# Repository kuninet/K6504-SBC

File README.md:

# K6504-SBC

## 概要

* R6504 CPU(6502 CPUの仲間)を使ったシングルボードコンピューターです。
  * アドレシングできる範囲は8kBです。
  * RAM4kB、ROM3kB UniversanMonitorを動かすのが目標です

## 回路図

## 基板製造データ

* プリント基板を製造するには、KiCAD/PCB フォルダに入っているzipファイルをお使いください。

## 部品表

[KiCAD/K6504-SBC.csv](KiCAD/K6504-SBC.csv)

## 注意点

* シリアルIC(6551)、RAM/IO/TIMER IC(6532)の割り込み信号線は、基板裏のソルダージャンパーをはんだで短絡すると有効になります。

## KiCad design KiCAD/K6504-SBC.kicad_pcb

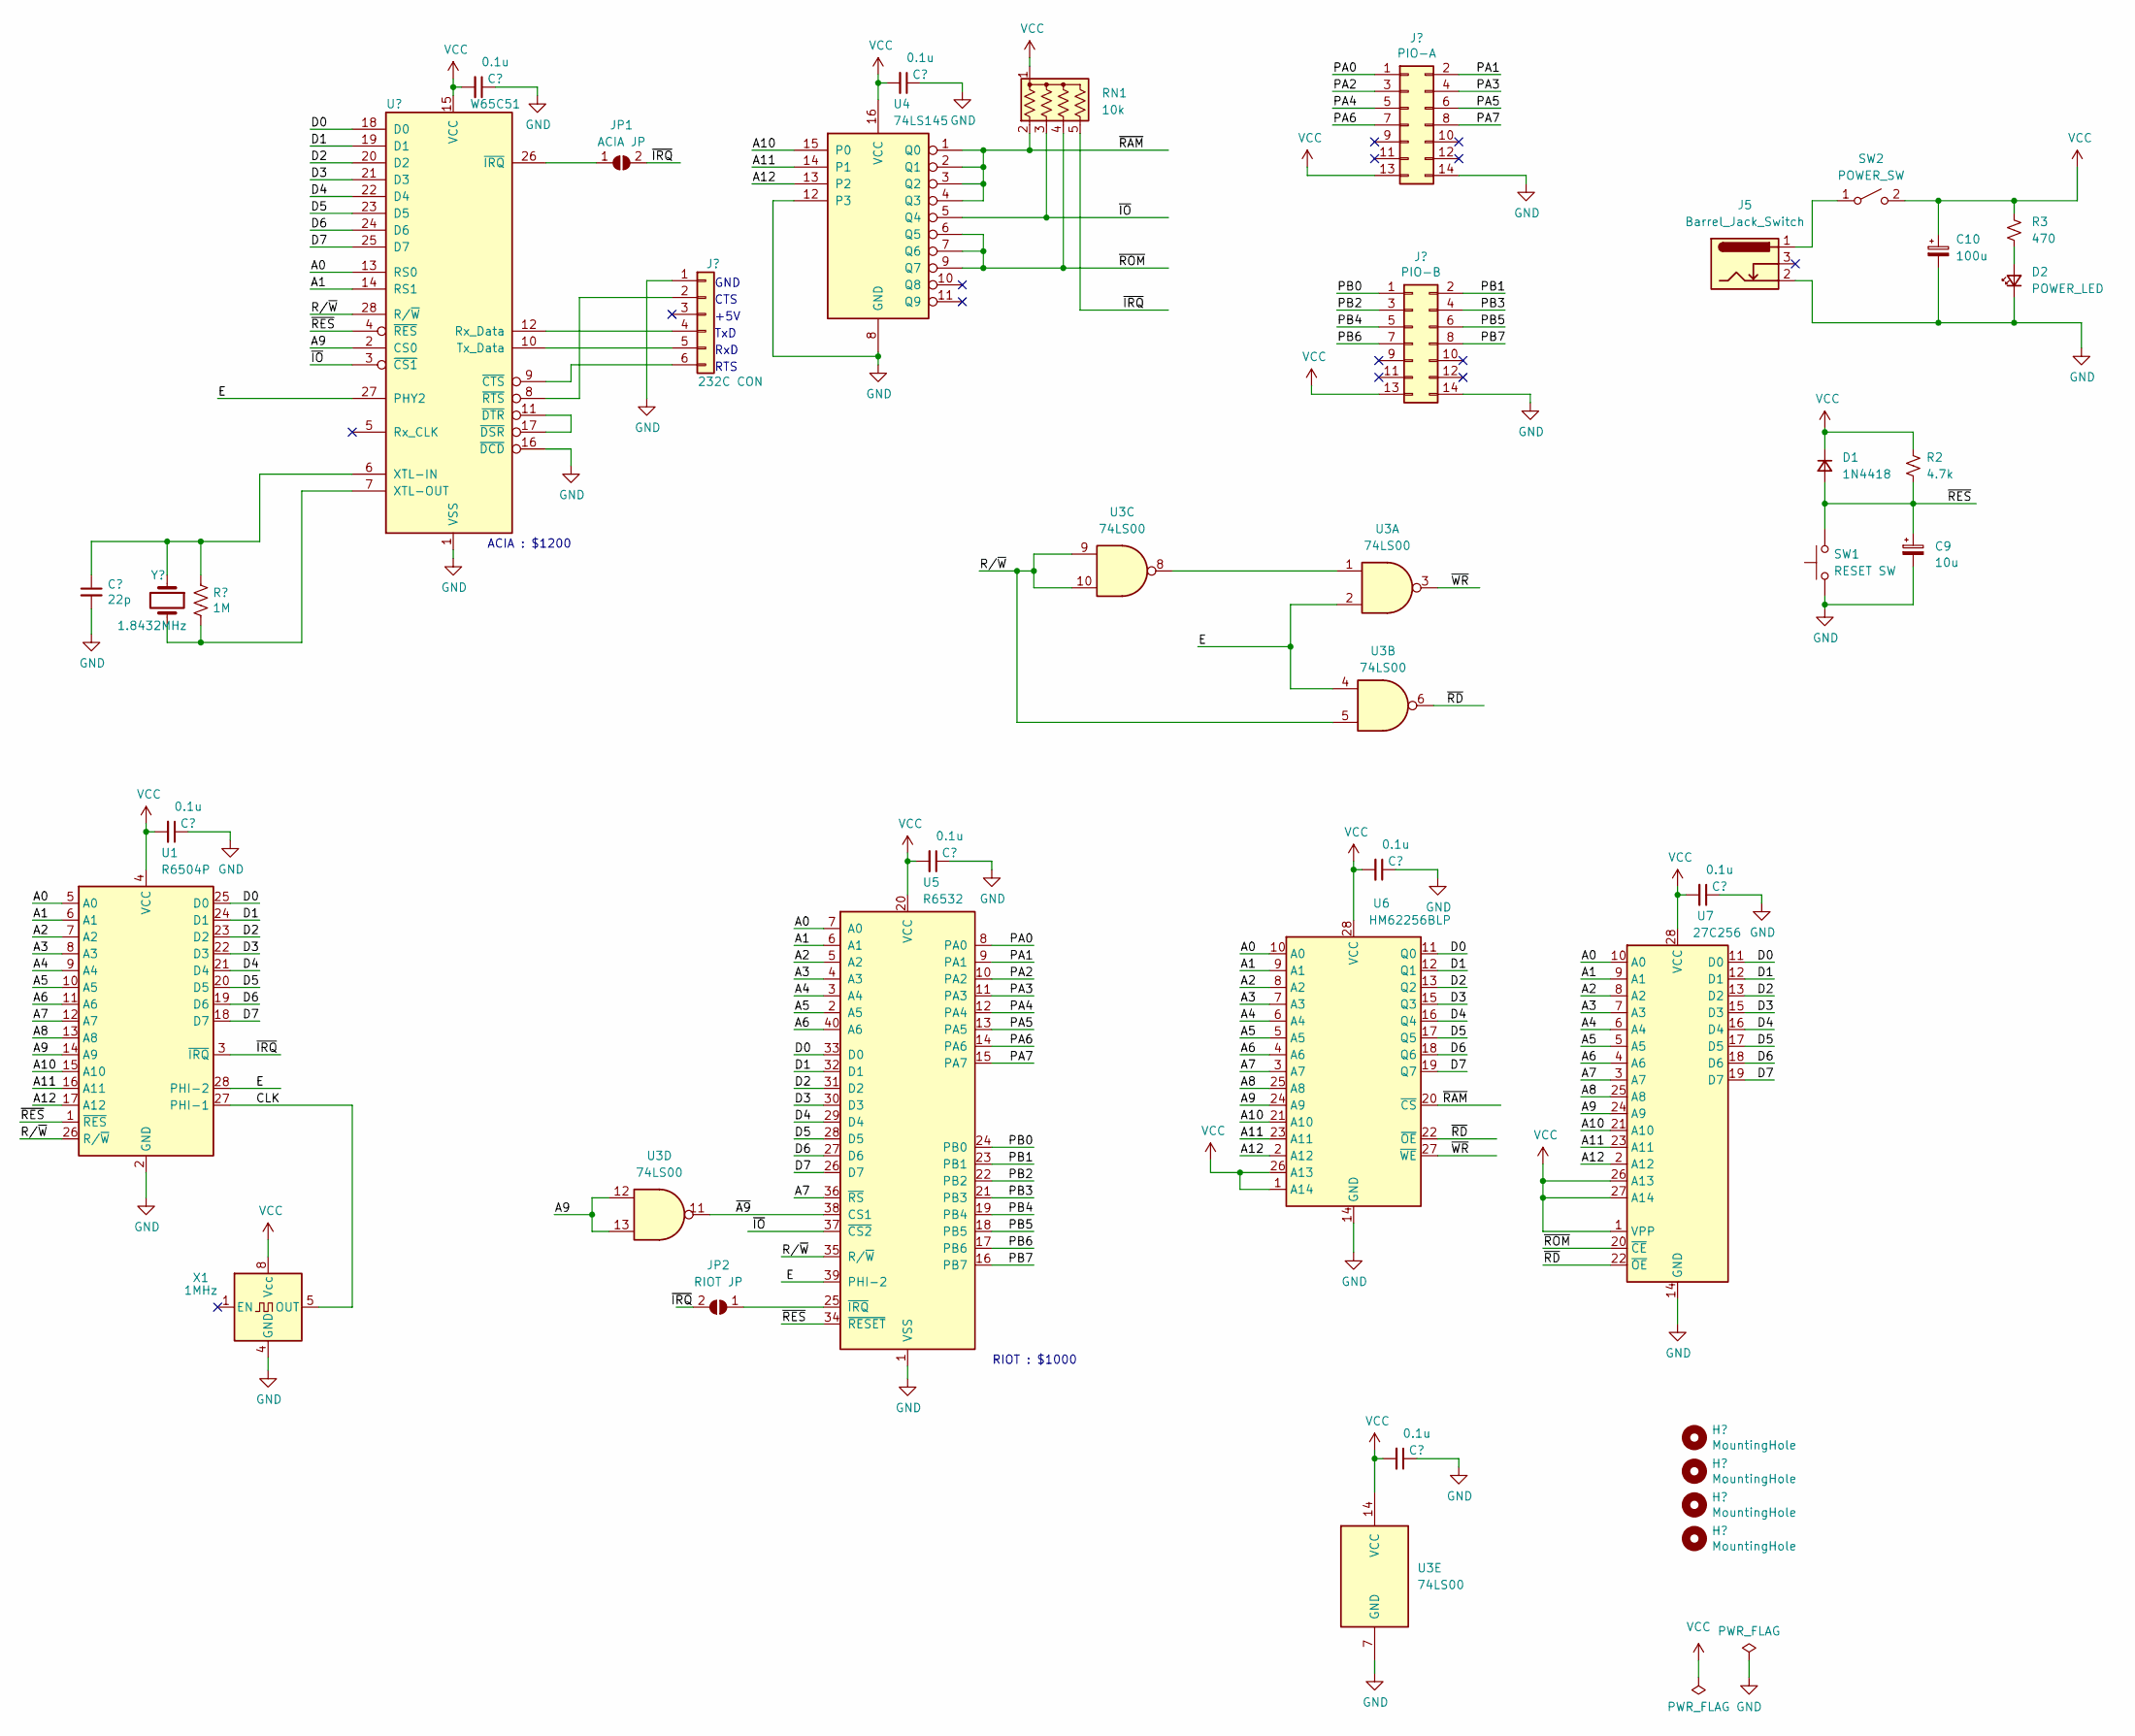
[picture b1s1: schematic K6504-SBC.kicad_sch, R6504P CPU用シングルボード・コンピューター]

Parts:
C1: 22p; C_Disc_D3.0mm_W1.6mm_P2.50mm
C2, C3, C4, C5, C6, C7, C8: 0.1u; C_Disc_D3.0mm_W1.6mm_P2.50mm
C9: 10u; CP_Radial_D5.0mm_P2.50mm
C10: 100u; CP_Radial_D8.0mm_P2.50mm
D1: 1N4418; D_DO-34_SOD68_P10.16mm_Horizontal
D2: POWER_LED; LED_D3.0mm
H1, H2, H3, H4: MountingHole; MountingHole_3.2mm_M3
J1: 232C CON; PinHeader_1x06_P2.54mm_Horizontal
J2: PIO-A; PinHeader_2x07_P2.54mm_Vertical
J4: PIO-B; PinHeader_2x07_P2.54mm_Vertical
J5: Barrel_Jack_Switch; BarrelJack_Horizontal
JP1: ACIA JP; SolderJumper-2_P1.3mm_Open_RoundedPad1.0x1.5mm
JP2: RIOT JP; SolderJumper-2_P1.3mm_Open_RoundedPad1.0x1.5mm
R1: 1M; R_Axial_DIN0204_L3.6mm_D1.6mm_P7.62mm_Horizontal
R2: 4.7k; R_Axial_DIN0207_L6.3mm_D2.5mm_P10.16mm_Horizontal
R3: 470; R_Axial_DIN0207_L6.3mm_D2.5mm_P10.16mm_Horizontal
RN1: 10k; R_Array_SIP5
SW1: RESET SW; SW_PUSH_6mm_H4.3mm
SW2: POWER_SW; PinHeader_1x03_P2.54mm_Vertical
U1: R6504P; DIP-28_W15.24mm_Socket
U2: W65C51; DIP-28_W15.24mm_Socket
U3: 74LS00; DIP-14_W7.62mm_Socket
U4: 74LS145; DIP-16_W7.62mm_Socket
U5: R6532; DIP-40_W15.24mm_Socket
U6: HM62256BLP; DIP-28_W15.24mm_Socket
U7: 27C256; DIP-28_W15.24mm_Socket
X1: 1MHz; Oscillator_DIP-8
Y1: 1.8432MHz; Crystal_HC49-U_Vertical

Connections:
/A0: U1.5 (A0), U2.13 (RS0), U5.7 (A0), U6.10 (A0), U7.10 (A0)
/A1: U1.6 (A1), U2.14 (RS1), U5.6 (A1), U6.9 (A1), U7.9 (A1)
/A2: U1.7 (A2), U5.5 (A2), U6.8 (A2), U7.8 (A2)
/A3: U1.8 (A3), U5.4 (A3), U6.7 (A3), U7.7 (A3)
/A4: U1.9 (A4), U5.3 (A4), U6.6 (A4), U7.6 (A4)
/A5: U1.10 (A5), U5.2 (A5), U6.5 (A5), U7.5 (A5)
/A6: U1.11 (A6), U5.40 (A6), U6.4 (A6), U7.4 (A6)
/A7: U1.12 (A7), U5.36 (~RS), U6.3 (A7), U7.3 (A7)
/A8: U1.13 (A8), U6.25 (A8), U7.25 (A8)
/A9: U1.14 (A9), U2.2 (CS0), U3.12, U3.13, U6.24 (A9), U7.24 (A9)
/A10: U1.15 (A10), U4.15 (P0), U6.21 (A10), U7.21 (A10)
/A11: U1.16 (A11), U4.14 (P1), U6.23 (A11), U7.23 (A11)
/A12: U1.17 (A12), U4.13 (P2), U6.2 (A12), U7.2 (A12)
/CLK: U1.27 (PHI-1), X1.5 (OUT)
/D0: U1.25 (D0), U2.18 (D0), U5.33 (D0), U6.11 (Q0), U7.11 (D0)
/D1: U1.24 (D1), U2.19 (D1), U5.32 (D1), U6.12 (Q1), U7.12 (D1)
/D2: U1.23 (D2), U2.20 (D2), U5.31 (D2), U6.13 (Q2), U7.13 (D2)
/D3: U1.22 (D3), U2.21 (D3), U5.30 (D3), U6.15 (Q3), U7.15 (D3)
/D4: U1.21 (D4), U2.22 (D4), U5.29 (D4), U6.16 (Q4), U7.16 (D4)
/D5: U1.20 (D5), U2.23 (D5), U5.28 (D5), U6.17 (Q5), U7.17 (D5)
/D6: U1.19 (D6), U2.24 (D6), U5.27 (D6), U6.18 (Q6), U7.18 (D6)
/D7: U1.18 (D7), U2.25 (D7), U5.26 (D7), U6.19 (Q7), U7.19 (D7)
/E: U1.28 (PHI-2), U2.27 (PHY2), U3.2, U3.4, U5.39 (PHI-2)
/PA0: J2.1, U5.8 (PA0)
/PA1: J2.2, U5.9 (PA1)
/PA2: J2.3, U5.10 (PA2)
/PA3: J2.4, U5.11 (PA3)
/PA4: J2.5, U5.12 (PA4)
/PA5: J2.6, U5.13 (PA5)
/PA6: J2.7, U5.14 (PA6)
/PA7: J2.8, U5.15 (PA7)
/PB0: J4.1, U5.24 (PB0)
/PB1: J4.2, U5.23 (PB1)
/PB2: J4.3, U5.22 (PB2)
/PB3: J4.4, U5.21 (PB3)
/PB4: J4.5, U5.19 (PB4)
/PB5: J4.6, U5.18 (PB5)
/PB6: J4.7, U5.17 (PB6)
/PB7: J4.8, U5.16 (PB7)
/R/~W: U1.26 (R/~W), U2.28 (R/~W), U3.5, U3.9, U3.10, U5.35 (R/~W)
/~A9: U3.11, U5.38 (CS1)
/~IO: RN1.3 (R2), U2.3 (~CS1), U4.5 (Q4), U5.37 (~CS2)
/~IRQ: JP1.2 (B), JP2.2 (B), RN1.5 (R4), U1.3 (~IRQ)
/~RAM: RN1.2 (R1), U4.1 (Q0), U4.2 (Q1), U4.3 (Q2), U4.4 (Q3), U6.20 (~CS)
/~RD: U3.6, U6.22 (~OE), U7.22 (~OE)
/~RES: C9.1, D1.2 (A), R2.2, SW1.2, U1.1 (~RES), U2.4 (~RES), U5.34 (~RESET)
/~ROM: RN1.4 (R3), U4.6 (Q5), U4.7 (Q6), U4.9 (Q7), U7.20 (~CE)
/~WR: U3.3, U6.27 (~WE)
GND: C1.2, C2.1, C3.1, C4.1, C5.1, C6.1, C7.1, C8.1, C9.2, C10.2, D2.1 (K), J1.1, J2.14, J4.14, J5.2, SW1.1, U1.2 (GND), U2.1 (VSS), U2.16 (~DCD), U3.7 (GND), U4.8 (GND), U4.12 (P3), U5.1 (VSS), U6.14 (GND), U7.14 (GND), X1.4 (GND)
unnamed: D2.2 (A), R3.2
unnamed: J1.2, U2.8 (~RTS)
unnamed: J1.4, U2.12 (Rx_Data)
unnamed: J1.5, U2.10 (Tx_Data)
unnamed: J1.6, U2.9 (~CTS)
unnamed: JP1.1 (A), U2.26 (~IRQ)
unnamed: JP2.1 (A), U5.25 (~IRQ)
unnamed: J5.1, SW2.1 (A)
unnamed: C1.1, R1.1, U2.6 (XTL-IN), Y1.1
unnamed: R1.2, U2.7 (XTL-OUT), Y1.2
unnamed: U2.11 (~DTR), U2.17 (~DSR)
unnamed: U3.1, U3.8
VCC: C2.2, C3.2, C4.2, C5.2, C6.2, C7.2, C8.2, C10.1, D1.1 (K), J2.13, J4.13, R2.1, R3.1, RN1.1 (common), SW2.2 (B), U1.4 (VCC), U2.15 (VCC), U3.14 (VCC), U4.16 (VCC), U5.20 (VCC), U6.1 (A14), U6.26 (A13), U6.28 (VCC), U7.1 (VPP), U7.26 (A13), U7.27 (A14), U7.28 (VCC), X1.8 (Vcc)

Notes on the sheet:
GND
RIOT : $1000
ACIA : $1200
RTS
RxD
+5V
CTS
TxD

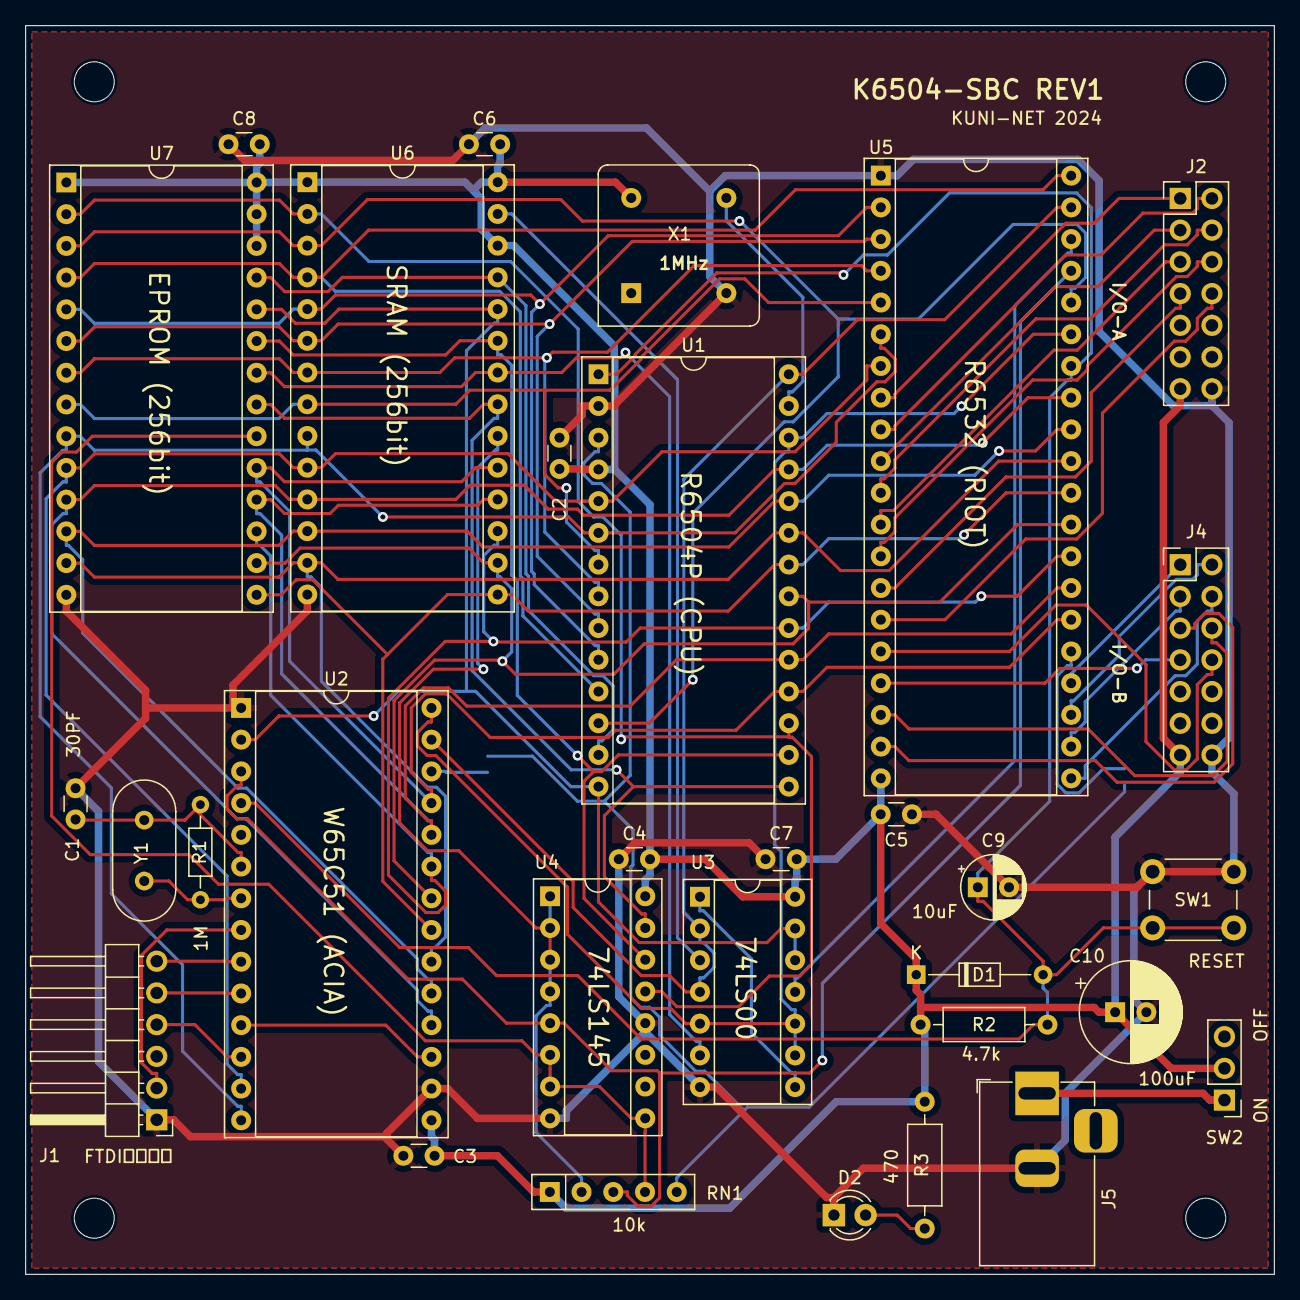
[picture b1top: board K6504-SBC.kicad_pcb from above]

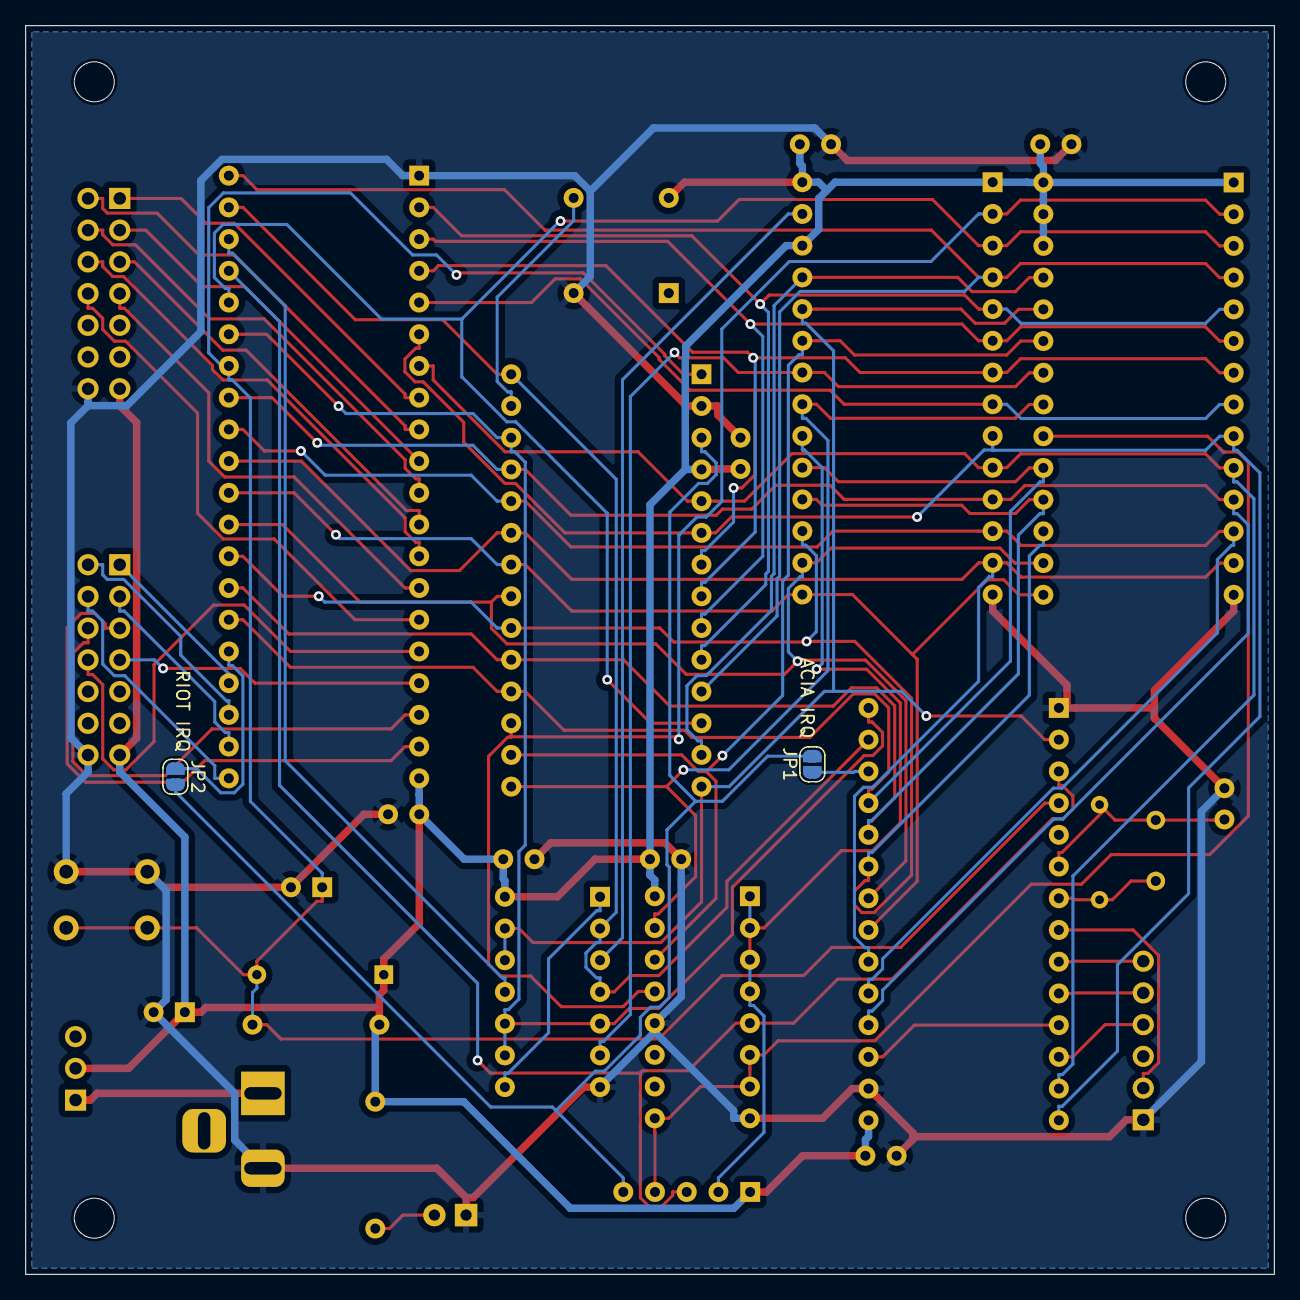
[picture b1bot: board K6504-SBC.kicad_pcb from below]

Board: 2 copper layers, 100.0 x 100.0 mm, 37 parts (2 on the bottom side), 62 nets.

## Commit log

2023-07-15 init
2023-10-01 KiCAD7で回路図作成、回路図イメージファイル添付
2024-02-23 メモリーマップ見直し & 回路図見直し
2024-02-23 回路図見直し
2024-02-24 回路図 : R6404シンボル間違い修正、IRQプルアップ忘れ修正
2024-02-24 部品との関連付け追加
2024-02-24 コンデンサ定数修正、回路図イメージ更新
2024-02-24 基板サイズ見直し、ガーバーデータ再出力
2024-02-24 部品表追加KiCAD\K6504-SBC.csv
2024-02-24 Create LICENSE
2024-05-19 動作確認等のサンプルソース追加
2024-05-19 サンプル ソース間違い修正
